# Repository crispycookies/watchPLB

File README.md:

# watchPLB
Open Source Emergency Beacon licensed under GPL-V3

Structure:
* Branch Samuel - Eagle Files
* Branch Firmware - Firmware files
  * In Firmware Directory there is a description of the folder Structure of the Firmware

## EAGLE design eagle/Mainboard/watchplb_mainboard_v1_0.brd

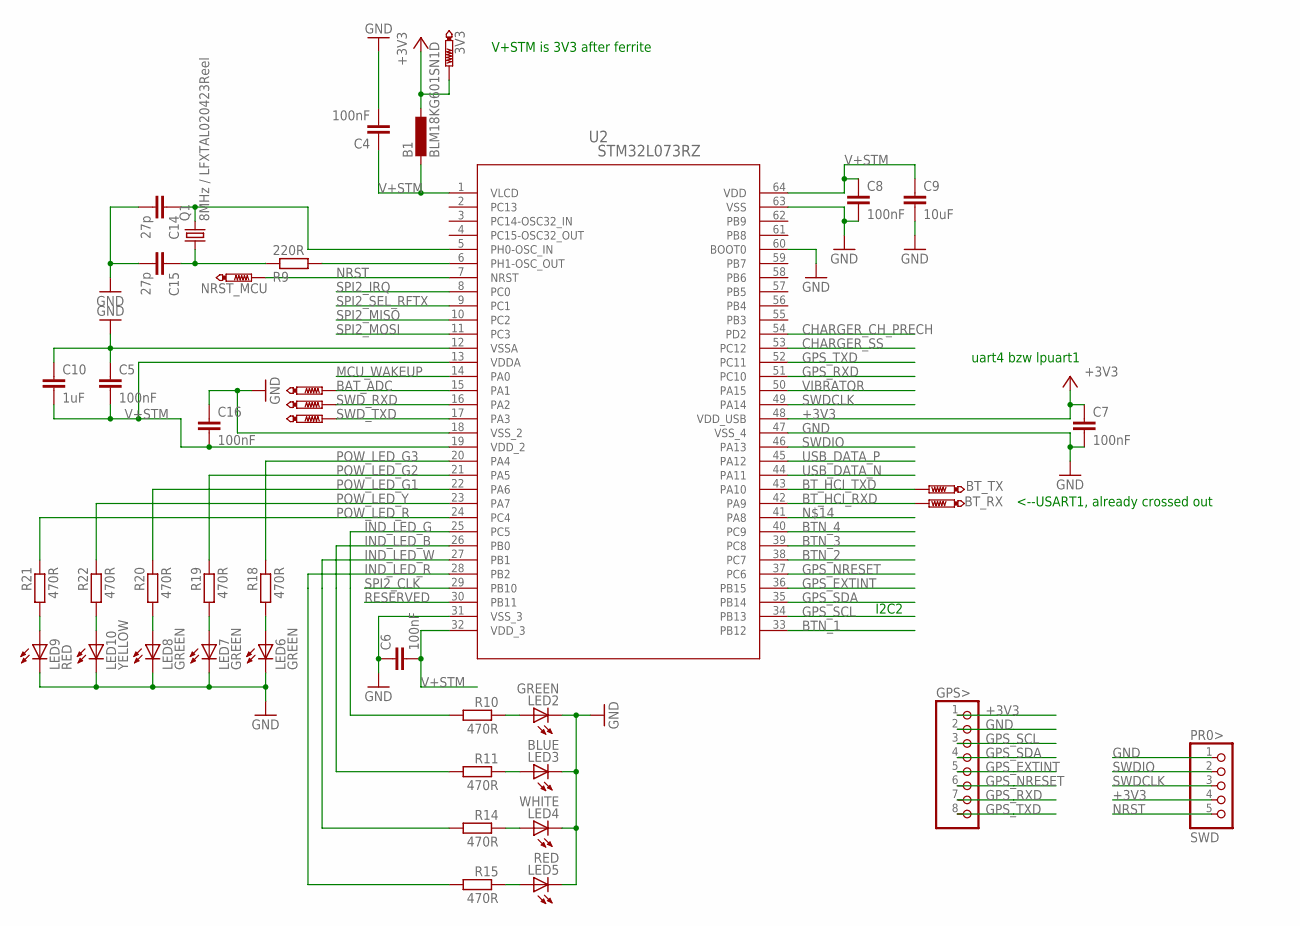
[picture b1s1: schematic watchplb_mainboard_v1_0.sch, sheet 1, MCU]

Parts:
3V3: PTR1B1,27; B1,27
B1: BLM18KG601SN1D; L0603
BAT_ADC: PTR1B1,27; B1,27
BT_RX: PTR1B1,27; B1,27
BT_TX: PTR1B1,27; B1,27
C4, C5, C6, C7, C8, C16: 100nF; C0805
C9: 10uF; C1206
C10: 1uF; C0805
C14, C15: 27p; C0805
GPS>: PINHD-1X8; 1X08
LED2, LED6, LED7, LED8: GREEN; CHIP-LED0805
LED3: BLUE; CHIP-LED0805
LED4: WHITE; CHIP-LED0805
LED5, LED9: RED; CHIP-LED0805
LED10: YELLOW; CHIP-LED0805
NRST_MCU: PTR1B1,27; B1,27
PR0>: SWD; 1X05
Q1: 8MHz / LFXTAL020423Reel; HC49UP
R9: 220R; M0805
R10, R11, R14, R15, R18, R19, R20, R21, R22: 470R; M0805
SWD_RXD: PTR1B1,27; B1,27
SWD_TXD: PTR1B1,27; B1,27
U2: STM32L073RZ; LQFP64-10X10MM

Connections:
+3V3: 3V3.TP, B1.1, C7.1, GPS>.1, PR0>.4, U2.48 (VDD_USB); also elsewhere on the board
BAT_ADC: BAT_ADC.TP, U2.15 (PA1); also elsewhere on the board
BTN_1: U2.33 (PB12); also elsewhere on the board
BTN_2: U2.38 (PC7); also elsewhere on the board
BTN_3: U2.39 (PC8); also elsewhere on the board
BTN_4: U2.40 (PC9); also elsewhere on the board
BT_HCI_RXD: BT_RX.TP, U2.42 (PA9); also elsewhere on the board
BT_HCI_TXD: BT_TX.TP, U2.43 (PA10); also elsewhere on the board
CHARGER_CH_PRECH: U2.54 (PD2); also elsewhere on the board
CHARGER_SS: U2.53 (PC12); also elsewhere on the board
GND: C4.2, C5.1, C6.1, C7.2, C8.2, C9.2, C10.1, C14.2, C15.2, C16.1, GPS>.2, LED2.C, LED3.C, LED4.C, LED5.C, LED6.C, LED7.C, LED8.C, LED9.C, LED10.C, PR0>.1, U2.12 (VSSA), U2.18 (VSS_2), U2.31 (VSS_3), U2.47 (VSS_4), U2.60 (BOOT0), U2.63 (VSS); also elsewhere on the board
GPS_EXTINT: GPS>.5, U2.36 (PB15)
GPS_NRESET: GPS>.6, U2.37 (PC6)
GPS_RXD: GPS>.7, U2.51 (PC10)
GPS_SCL: GPS>.3, U2.34 (PB13)
GPS_SDA: GPS>.4, U2.35 (PB14)
GPS_TXD: GPS>.8, U2.52 (PC11)
IND_LED_B: R11.2, U2.26 (PB0)
IND_LED_G: R10.2, U2.25 (PC5)
IND_LED_R: R15.2, U2.28 (PB2)
IND_LED_W: R14.2, U2.27 (PB1)
MCU_WAKEUP: U2.14 (PA0); also elsewhere on the board
unnamed: LED2.A, R10.1
unnamed: LED3.A, R11.1
unnamed: C15.1, Q1.1, R9.1
unnamed: C14.1, Q1.2, U2.5 (PH0-OSC_IN)
unnamed: R9.2, U2.6 (PH1-OSC_OUT)
unnamed: LED4.A, R14.1
unnamed: LED9.A, R21.2
unnamed: LED5.A, R15.1
unnamed: LED6.A, R18.2
unnamed: LED7.A, R19.2
unnamed: LED10.A, R22.2
unnamed: LED8.A, R20.2
NRST: NRST_MCU.TP, PR0>.5, U2.7 (NRST); also elsewhere on the board
POW_LED_G1: R20.1, U2.22 (PA6)
POW_LED_G2: R19.1, U2.21 (PA5)
POW_LED_G3: R18.1, U2.20 (PA4)
POW_LED_R: R21.1, U2.24 (PC4)
POW_LED_Y: R22.1, U2.23 (PA7)
RESERVED: U2.30 (PB11)
SPI2_CLK: U2.29 (PB10); also elsewhere on the board
SPI2_IRQ: U2.8 (PC0); also elsewhere on the board
SPI2_MISO: U2.10 (PC2); also elsewhere on the board
SPI2_MOSI: U2.11 (PC3); also elsewhere on the board
SPI2_SEL_RFTX: U2.9 (PC1); also elsewhere on the board
SWDCLK: PR0>.3, U2.49 (PA14)
SWDIO: PR0>.2, U2.46 (PA13)
SWD_RXD: SWD_RXD.TP, U2.16 (PA2)
SWD_TXD: SWD_TXD.TP, U2.17 (PA3)
USB_DATA_N: U2.44 (PA11); also elsewhere on the board
USB_DATA_P: U2.45 (PA12); also elsewhere on the board
V+STM: B1.2, C4.1, C5.2, C6.2, C8.1, C9.1, C10.2, C16.2, U2.1 (VLCD), U2.13 (VDDA), U2.19 (VDD_2), U2.32 (VDD_3), U2.64 (VDD)
VIBRATOR: U2.50 (PA15); also elsewhere on the board

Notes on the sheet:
<--USART1, already crossed out
I2C2
uart4 bzw lpuart1
V+STM is 3V3 after ferrite

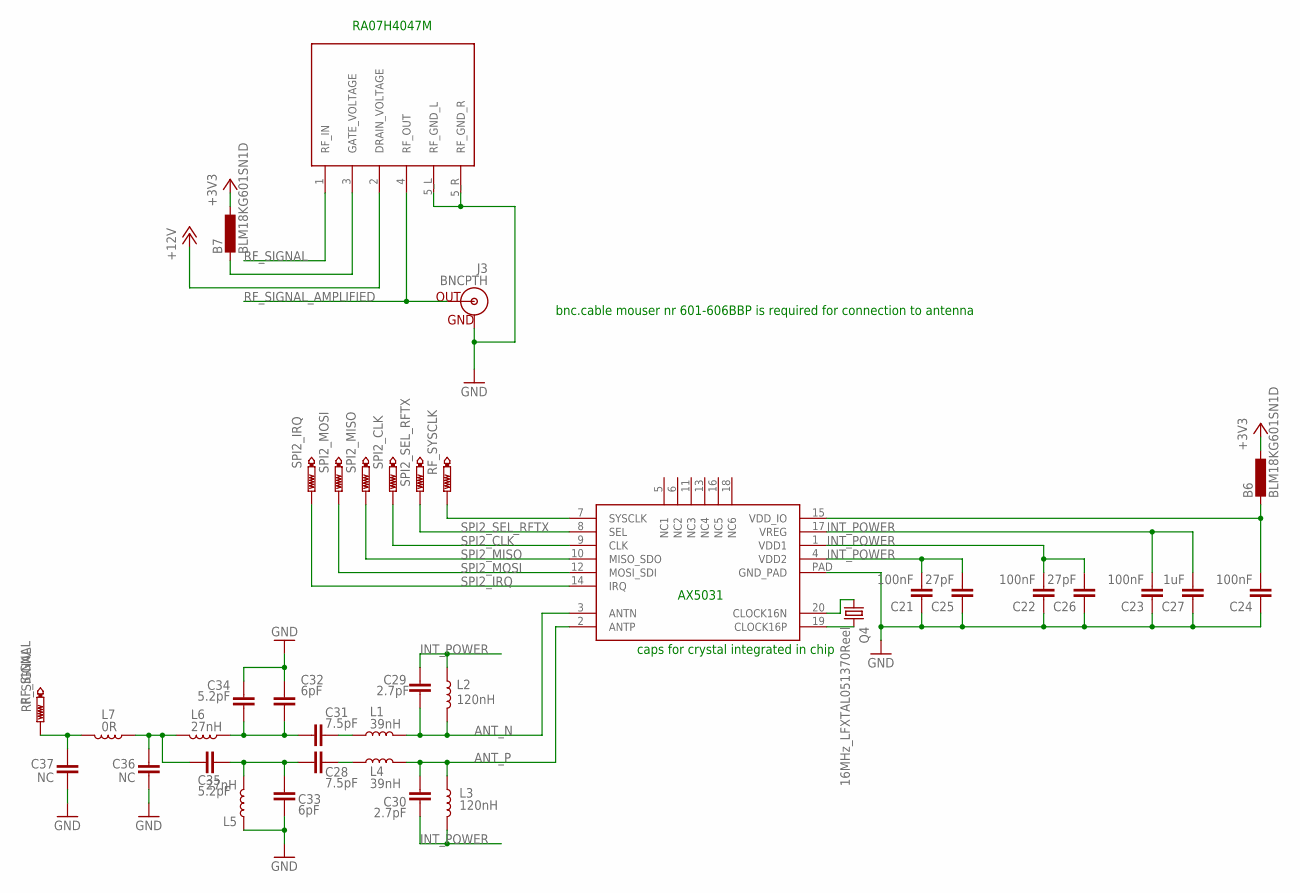
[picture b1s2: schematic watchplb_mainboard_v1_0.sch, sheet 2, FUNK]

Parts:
B6, B7: BLM18KG601SN1D; L0603
C21, C22, C23, C24: 100nF; C0805
C25, C26: 27pF; C0805
C27: 1uF; C0805
C28, C31: 7.5pF; C0805
C29, C30: 2.7pF; C0805
C32, C33: 6pF; C0805
C34, C35: 5.2pF; C0805
C36, C37: NC; C0805
IC4: AX5031; QFN20
J3: BNCPTH; BNC
L1, L4: 39nH; 0805
L2, L3: 120nH; 0805
L5, L6: 27nH; 0805
L7: 0R; 0805
Q4: 16MHz_LFXTAL051370Reel; HC49UP
RF_SIGNAL: PTR1B2,54; B2,54
RF_SYSCLK: PTR1B1,27; B1,27
SPI2_CLK, SPI2_IRQ, SPI2_MISO, SPI2_MOSI, SPI2_SEL_RFTX: PTR1B1,27; B1,27
U$2: RA07H4047M

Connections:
+3V3: B6.1, B7.1; also elsewhere on the board
+12V: U$2.2 (DRAIN_VOLTAGE); also elsewhere on the board
ANT_N: C29.1, IC4.3 (ANTN), L1.2, L2.2
ANT_P: C30.2, IC4.2 (ANTP), L3.1, L4.2
GND: C21.1, C22.1, C23.1, C24.1, C25.1, C26.1, C27.1, C32.1, C33.2, C34.1, C36.1, C37.1, IC4.PAD (GND_PAD), J3.GND, L5.1, U$2.5_L (RF_GND_L), U$2.5_R (RF_GND_R); also elsewhere on the board
INT_POWER: C21.2, C22.2, C23.2, C25.2, C26.2, C27.2, C29.2, C30.1, IC4.1 (VDD1), IC4.4 (VDD2), IC4.17 (VREG), L2.1, L3.2
unnamed: IC4.19 (CLOCK16P), Q4.2
unnamed: IC4.20 (CLOCK16N), Q4.1
unnamed: IC4.7 (SYSCLK), RF_SYSCLK.TP
unnamed: C28.1, L4.1
unnamed: C31.1, L1.1
unnamed: C31.2, C32.2, C34.2, L6.1
unnamed: C28.2, C33.1, C35.2, L5.2
unnamed: C35.1, C36.2, L6.2, L7.1
unnamed: B6.2, C24.2, IC4.15 (VDD_IO)
unnamed: B7.2, U$2.3 (GATE_VOLTAGE)
RF_SIGNAL: C37.2, L7.2, RF_SIGNAL.TP, U$2.1 (RF_IN)
RF_SIGNAL_AMPLIFIED: J3.S (OUT), U$2.4 (RF_OUT)
SPI2_CLK: IC4.9 (CLK), SPI2_CLK.TP; also elsewhere on the board
SPI2_IRQ: IC4.14 (IRQ), SPI2_IRQ.TP; also elsewhere on the board
SPI2_MISO: IC4.10 (MISO_SDO), SPI2_MISO.TP; also elsewhere on the board
SPI2_MOSI: IC4.12 (MOSI_SDI), SPI2_MOSI.TP; also elsewhere on the board
SPI2_SEL_RFTX: IC4.8 (SEL), SPI2_SEL_RFTX.TP; also elsewhere on the board

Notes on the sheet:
caps for crystal integrated in chip
bnc.cable mouser nr 601-606BBP is required for connection to antenna
AX5031
RA07H4047M

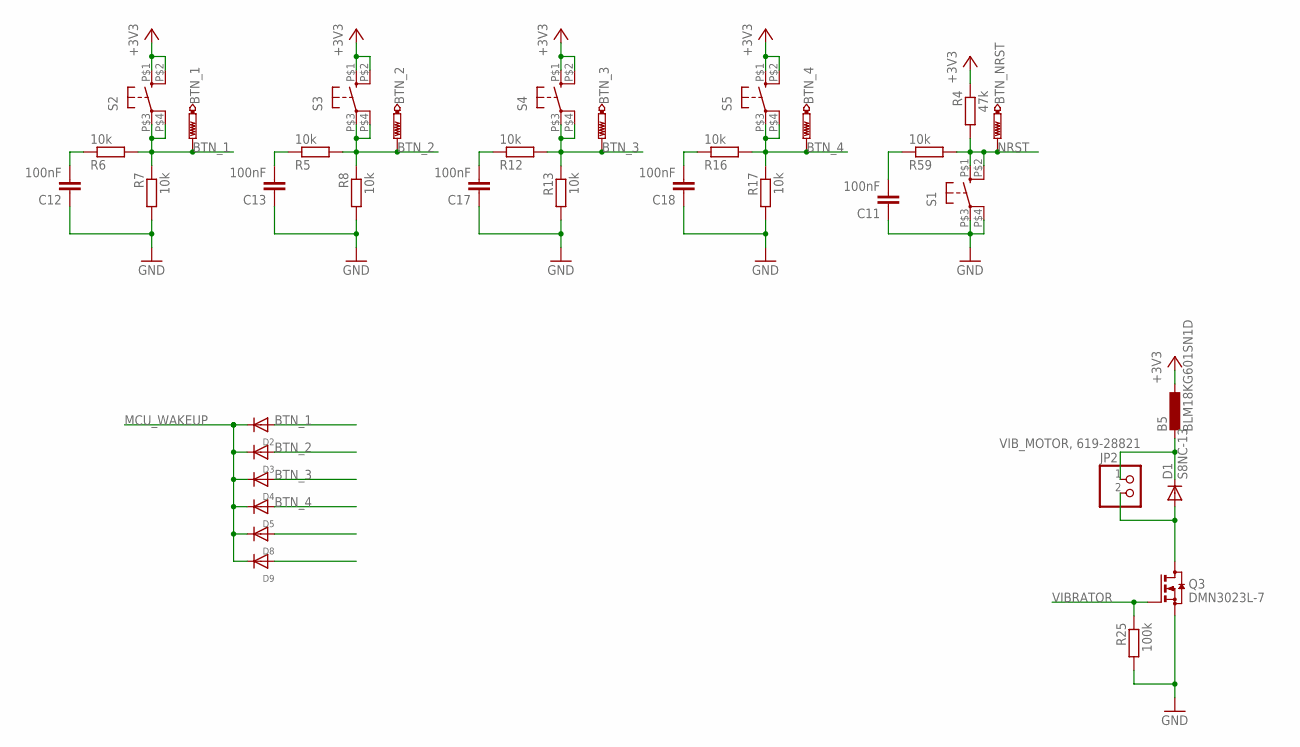
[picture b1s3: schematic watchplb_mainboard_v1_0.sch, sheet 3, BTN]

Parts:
B5: BLM18KG601SN1D; L0603
BTN_1, BTN_2, BTN_3, BTN_4: PTR1B1,27; B1,27
BTN_NRST: PTR1B1,27; B1,27
C11, C12, C13, C17, C18: 100nF; C0805
D1: S8NC-13; SMC
D2, D3, D4, D5, D8, D9: DIODESOD-123; SOD-123
JP2: VIB_MOTOR, 619-28821; 1X02
Q3: DMN3023L-7; SOT23
R4: 47k; M0805
R5, R6, R7, R8, R12, R13, R16, R17, R59: 10k; M0805
R25: 100k; M0805
S1, S2, S3, S4, S5: TL3305; SMD_SWITCH

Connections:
+3V3: B5.1, R4.1, S2.P$1 (SL1), S2.P$2 (SL2), S3.P$1 (SL1), S3.P$2 (SL2), S4.P$1 (SL1), S4.P$2 (SL2), S5.P$1 (SL1), S5.P$2 (SL2); also elsewhere on the board
BTN_1: BTN_1.TP, D2.A, R6.2, R7.1, S2.P$3 (SR1), S2.P$4 (SR2); also elsewhere on the board
BTN_2: BTN_2.TP, D3.A, R5.2, R8.1, S3.P$3 (SR1), S3.P$4 (SR2); also elsewhere on the board
BTN_3: BTN_3.TP, D4.A, R12.2, R13.1, S4.P$3 (SR1), S4.P$4 (SR2); also elsewhere on the board
BTN_4: BTN_4.TP, D5.A, R16.2, R17.1, S5.P$3 (SR1), S5.P$4 (SR2); also elsewhere on the board
GND: C11.1, C12.1, C13.1, C17.1, C18.1, Q3.2 (S), R7.2, R8.2, R13.2, R17.2, R25.2, S1.P$3 (SR1), S1.P$4 (SR2); also elsewhere on the board
MCU_WAKEUP: D2.C, D3.C, D4.C, D5.C, D8.C, D9.C; also elsewhere on the board
unnamed: C12.2, R6.1
unnamed: C13.2, R5.1
unnamed: C17.2, R12.1
unnamed: C18.2, R16.1
unnamed: D1.A, JP2.2, Q3.3 (D)
unnamed: B5.2, D1.C, JP2.1
unnamed: C11.2, R59.1
NRST: BTN_NRST.TP, R4.2, R59.2, S1.P$1 (SL1), S1.P$2 (SL2); also elsewhere on the board
VIBRATOR: Q3.1 (G), R25.1; also elsewhere on the board

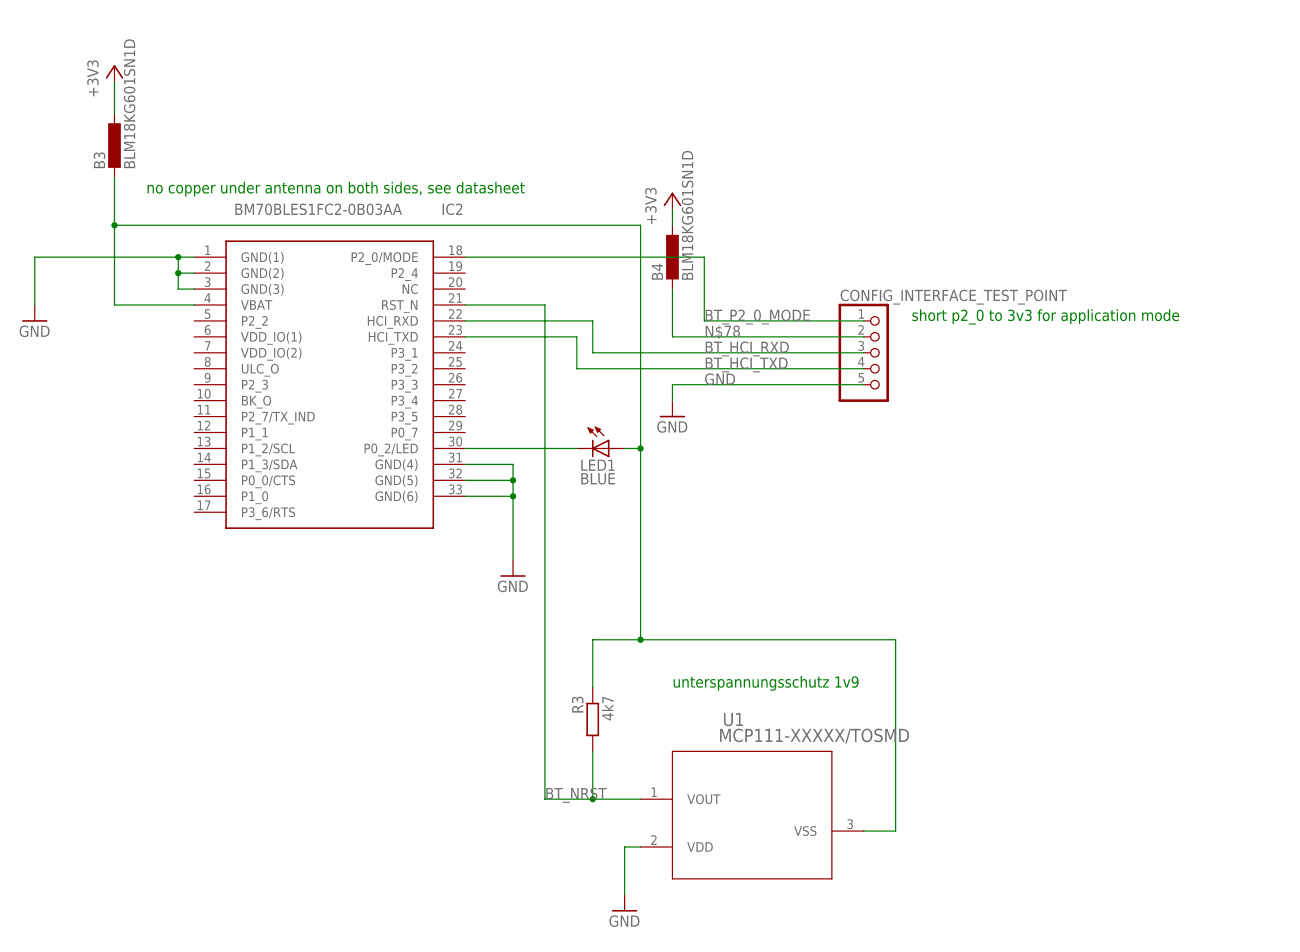
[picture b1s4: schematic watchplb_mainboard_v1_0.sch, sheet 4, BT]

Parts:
B3, B4: BLM18KG601SN1D; L0603
CONFIG_INTERFACE_TEST_POINT: PINHD-1X5; 1X05
IC2: BM70BLES1FC2-0B03AA; BM78SPPS5NC2_1
LED1: BLUE; CHIP-LED0805
R3: 4k7; M0805
U1: MCP111-XXXXX/TOSMD; SC70-3-R

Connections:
+3V3: B3.1, B4.1; also elsewhere on the board
BT_HCI_RXD: CONFIG_INTERFACE_TEST_POINT.3, IC2.22 (HCI_RXD); also elsewhere on the board
BT_HCI_TXD: CONFIG_INTERFACE_TEST_POINT.4, IC2.23 (HCI_TXD); also elsewhere on the board
BT_NRST: IC2.21 (RST_N), R3.2, U1.1 (VOUT)
BT_P2_0_MODE: CONFIG_INTERFACE_TEST_POINT.1, IC2.18 (P2_0/MODE)
GND: CONFIG_INTERFACE_TEST_POINT.5, IC2.1 (GND(1)), IC2.2 (GND(2)), IC2.3 (GND(3)), IC2.31 (GND(4)), IC2.32 (GND(5)), IC2.33 (GND(6)), U1.2 (VDD); also elsewhere on the board
unnamed: IC2.30 (P0_2/LED), LED1.C
unnamed: B4.2, CONFIG_INTERFACE_TEST_POINT.2
unnamed: B3.2, IC2.4 (VBAT), LED1.A, R3.1, U1.3 (VSS)

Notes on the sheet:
unterspannungsschutz 1v9
no copper under antenna on both sides, see datasheet
short p2_0 to 3v3 for application mode

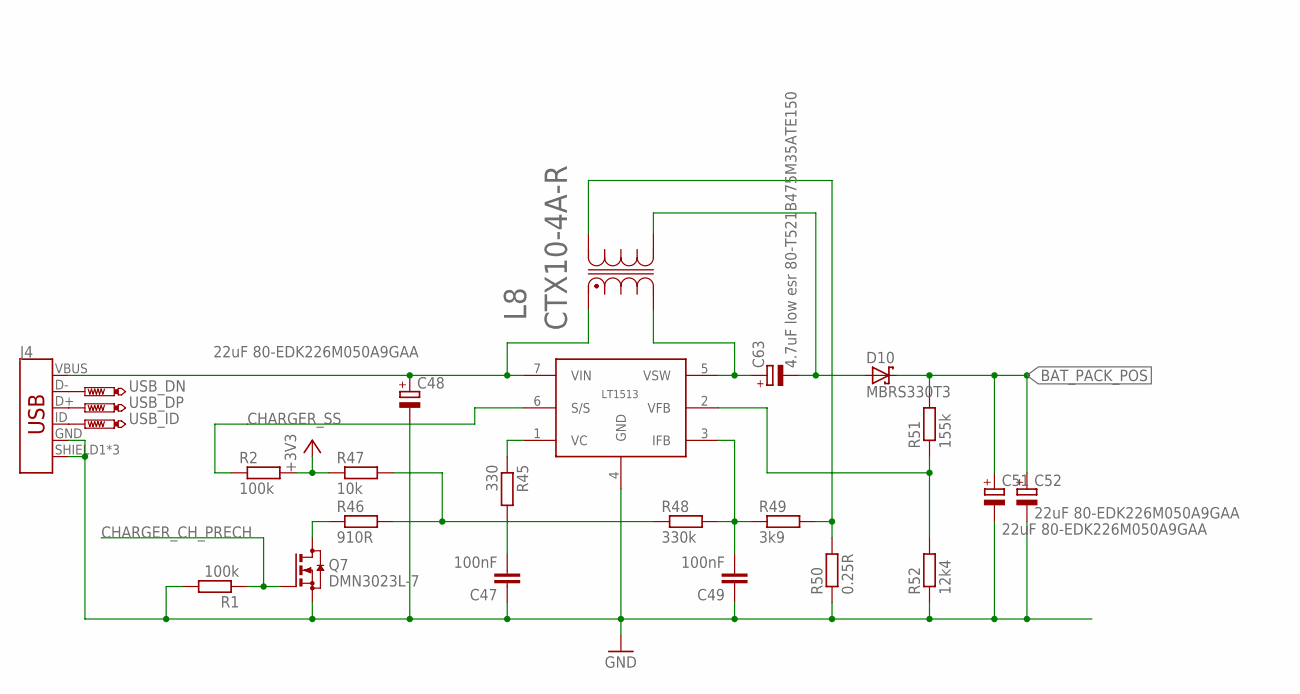
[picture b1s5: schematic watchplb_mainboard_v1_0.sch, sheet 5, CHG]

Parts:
C47, C49: 100nF; C0805K
C48, C51, C52: 22uF 80-EDK226M050A9GAA; PANASONIC_E
C63: 4.7uF low esr 80-T521B475M35ATE150; B/3528-21R
D10: MBRS330T3; SMC
IC1: LT1513; TO220-7
J4: USB_MICRO-B_FEMALE-SMT; USB-B-MICRO-SMD
L8: CTX10-4A-R; INDM115115X635N
Q7: DMN3023L-7; SOT23
R1, R2: 100k; M0805
R45: 330; M0805
R46: 910R; M0805
R47: 10k; M0805
R48: 330k; M0805
R49: 3k9; M0805
R50: 0.25R; R2512
R51: 155k; M0805
R52: 12k4; M0805
USB_DN: PTR1B1,27; B1,27
USB_DP: PTR1B1,27; B1,27
USB_ID: PTR1B1,27; B1,27

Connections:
+3V3: R2.2, R47.1; also elsewhere on the board
BAT_PACK_POS: C51.+, C52.+, D10.C, R51.2; also elsewhere on the board
CHARGER_CH_PRECH: Q7.1 (G), R1.1; also elsewhere on the board
CHARGER_SS: IC1.6 (S/S), R2.1; also elsewhere on the board
GND: C47.1, C48.-, C49.1, C51.-, C52.-, IC1.4 (GND), J4.GND, J4.SHIELD1 (SHIELD), J4.SHIELD2 (SHIELD), J4.SHIELD3 (SHIELD), Q7.2 (S), R1.2, R50.1, R52.1; also elsewhere on the board
unnamed: C63.+, IC1.5 (VSW), L8.2
unnamed: C48.+, IC1.7 (VIN), J4.VBUS, L8.1
unnamed: L8.4, R49.2, R50.2
unnamed: C47.2, R45.2
unnamed: IC1.1 (VC), R45.1
unnamed: Q7.3 (D), R46.1
unnamed: R46.2, R47.2, R48.1
unnamed: C49.2, IC1.3 (IFB), R48.2, R49.1
unnamed: IC1.2 (VFB), R51.1, R52.2
unnamed: J4.ID, USB_ID.TP
unnamed: J4.D+, USB_DP.TP
unnamed: J4.D-, USB_DN.TP
unnamed: C63.-, D10.A, L8.3

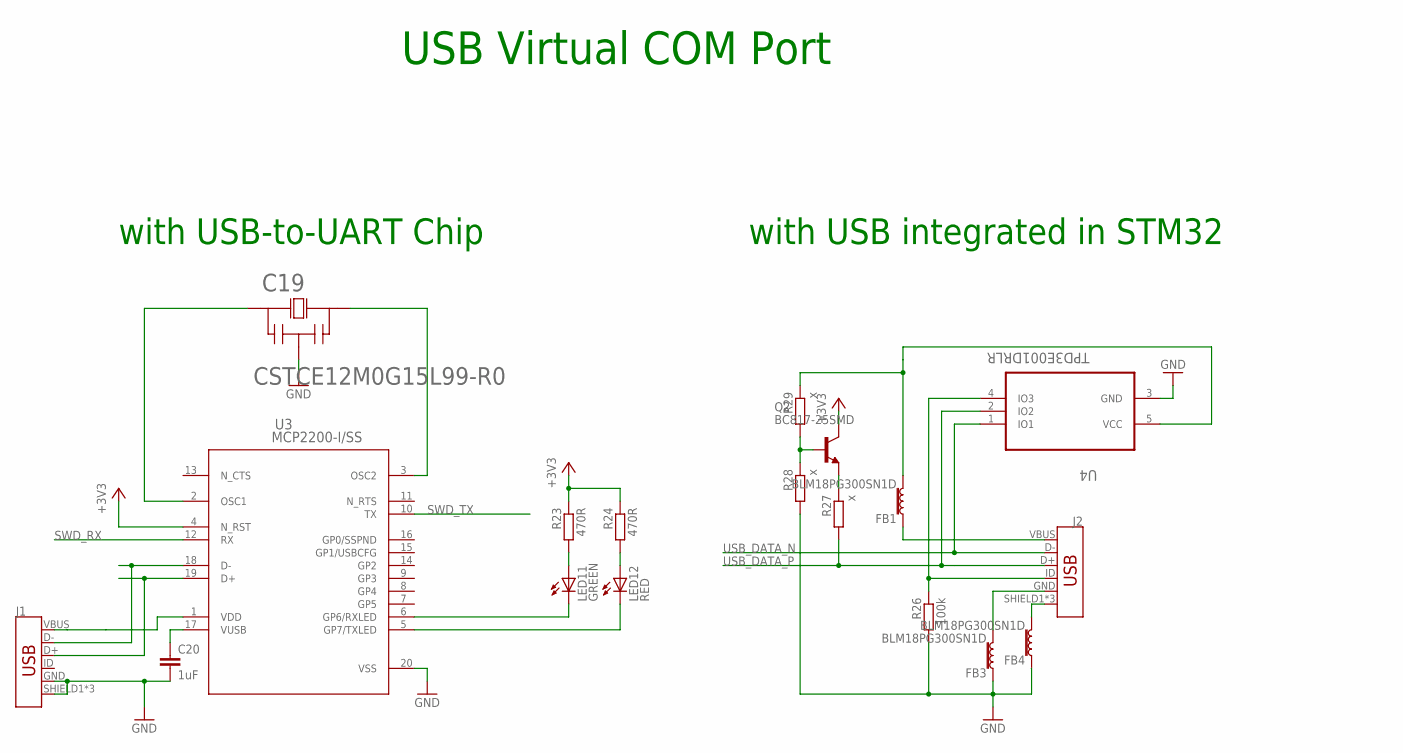
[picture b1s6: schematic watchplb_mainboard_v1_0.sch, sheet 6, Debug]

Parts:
C19: CSTCE12M0G15L99-R0; CSTCE
C20: 1uF; C0805
FB1, FB3, FB4: BLM18PG300SN1D; 0603
J1, J2: USB_MICRO-B_FEMALE-SMT; USB-B-MICRO-SMD
LED11: GREEN; CHIP-LED0805
LED12: RED; CHIP-LED0805
Q2: BC817-25SMD; SOT23-BEC
R23, R24: 470R; M0805
R26: 100k; M0805
R27, R28, R29: x; M0805
U3: MCP2200-I/SS; SSOP20_MC
U4: TPD3E001DRLR; SOT50P160X60-5N

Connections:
+3V3: Q2.C, R23.1, R24.1, U3.4 (N_RST); also elsewhere on the board
GND: C19.2 (22), C20.2, FB3.1, FB4.1, J1.GND, J1.SHIELD1 (SHIELD), J1.SHIELD2 (SHIELD), J1.SHIELD3 (SHIELD), R26.2, R28.2, U3.20 (VSS), U4.3 (GND); also elsewhere on the board
unnamed: LED11.A, R23.2
unnamed: C19.3 (33), U3.3 (OSC2)
unnamed: C19.1 (11), U3.2 (OSC1)
unnamed: J1.D-, U3.18 (D-)
unnamed: J1.D+, U3.19 (D+)
unnamed: C20.1, U3.17 (VUSB)
unnamed: LED12.A, R24.2
unnamed: LED11.C, U3.6 (GP6/RXLED)
unnamed: LED12.C, U3.5 (GP7/TXLED)
unnamed: FB4.2, J2.SHIELD1 (SHIELD), J2.SHIELD2 (SHIELD), J2.SHIELD3 (SHIELD)
unnamed: FB3.2, J2.GND
unnamed: FB1.1, J2.VBUS
unnamed: J2.ID, R26.1, U4.4 (IO3)
unnamed: Q2.E, R27.1
unnamed: Q2.B, R28.1, R29.2
unnamed: J1.VBUS, U3.1 (VDD)
unnamed: FB1.2, R29.1, U4.5 (VCC)
SWD_RX: U3.12 (RX)
SWD_TX: U3.10 (TX)
USB_DATA_N: J2.D-, U4.1 (IO1); also elsewhere on the board
USB_DATA_P: J2.D+, R27.2, U4.2 (IO2); also elsewhere on the board

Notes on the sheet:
USB Virtual COM Port
with USB integrated in STM32
with USB-to-UART Chip

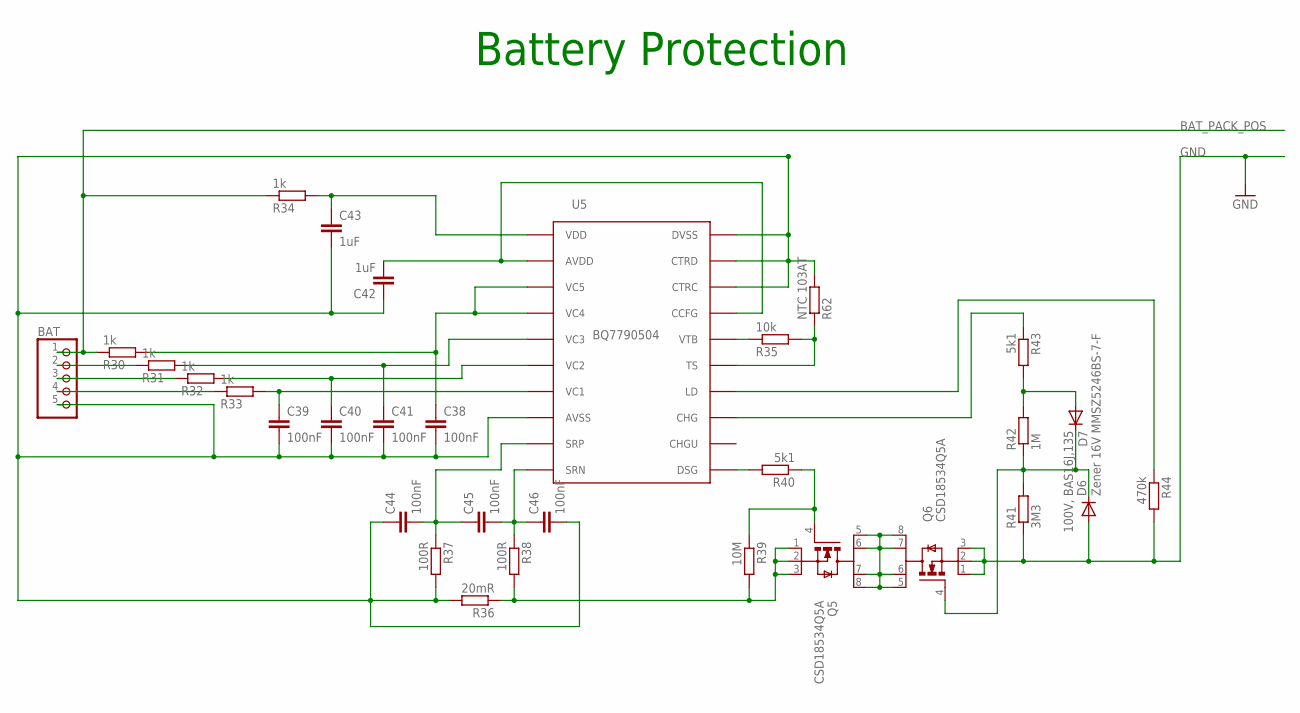
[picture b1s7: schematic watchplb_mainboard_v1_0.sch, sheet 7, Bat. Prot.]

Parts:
BAT: PINHD-1X5; 1X05
C38, C39, C40, C41, C44, C45, C46: 100nF; C0805K
C42, C43: 1uF; C0805K
D6: Zener 16V MMSZ5246BS-7-F; SOD323-R
D7: 100V, BAS16J,135; SOD323-R
Q5, Q6: CSD18534Q5A; TRANS_CSD18534Q5A
R30, R31, R32, R33, R34: 1k; M0805
R35: 10k; M0805
R36: 20mR; R2512
R37, R38: 100R; M0805
R39: 10M; M0805
R40, R43: 5k1; M0805
R41: 3M3; M0805
R42: 1M; M0805
R44: 470k; M0805
R62: NTC 103AT; M0805
U5: BQ7790504; TSSOP-20/6MM

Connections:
BAT_PACK_GND: BAT.5, C38.2, C39.2, C40.2, C41.2, C42.1, C43.2, C44.1, C46.2, R36.2, R37.2, R62.2, U5.8 (AVSS), U5.18 (CTRC), U5.19 (CTRD), U5.20 (DVSS)
BAT_PACK_POS: BAT.1, R30.1, R34.1; also elsewhere on the board
GND: D6.A, Q6.1, Q6.2, Q6.3, R41.1, R44.2; also elsewhere on the board
unnamed: R35.2, R62.1, U5.15 (TS)
unnamed: D6.C, D7.C, Q6.4, R41.2, R42.1
unnamed: BAT.2, R31.1
unnamed: BAT.3, R32.1
unnamed: BAT.4, R33.1
unnamed: C39.1, R33.2, U5.7 (VC1)
unnamed: C40.1, R32.2, U5.6 (VC2)
unnamed: C41.1, R31.2, U5.5 (VC3)
unnamed: C38.1, R30.2, U5.3 (VC5), U5.4 (VC4)
unnamed: C43.1, R34.2, U5.1 (VDD)
unnamed: Q5.1, Q5.2, Q5.3, R36.1, R38.2, R39.2
unnamed: C42.2, U5.2 (AVDD), U5.17 (CCFG)
unnamed: C45.2, C46.1, R38.1, U5.10 (SRN)
unnamed: C44.2, C45.1, R37.1, U5.9 (SRP)
unnamed: Q5.5, Q5.6, Q5.7, Q5.8, Q6.5, Q6.6, Q6.7, Q6.8
unnamed: R35.1, U5.16 (VTB)
unnamed: Q5.4, R39.1, R40.1
unnamed: R40.2, U5.11 (DSG)
unnamed: D7.A, R42.2, R43.2
unnamed: R43.1, U5.13 (CHG)
unnamed: R44.1, U5.14 (LD)

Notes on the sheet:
BQ7790504
Battery Protection

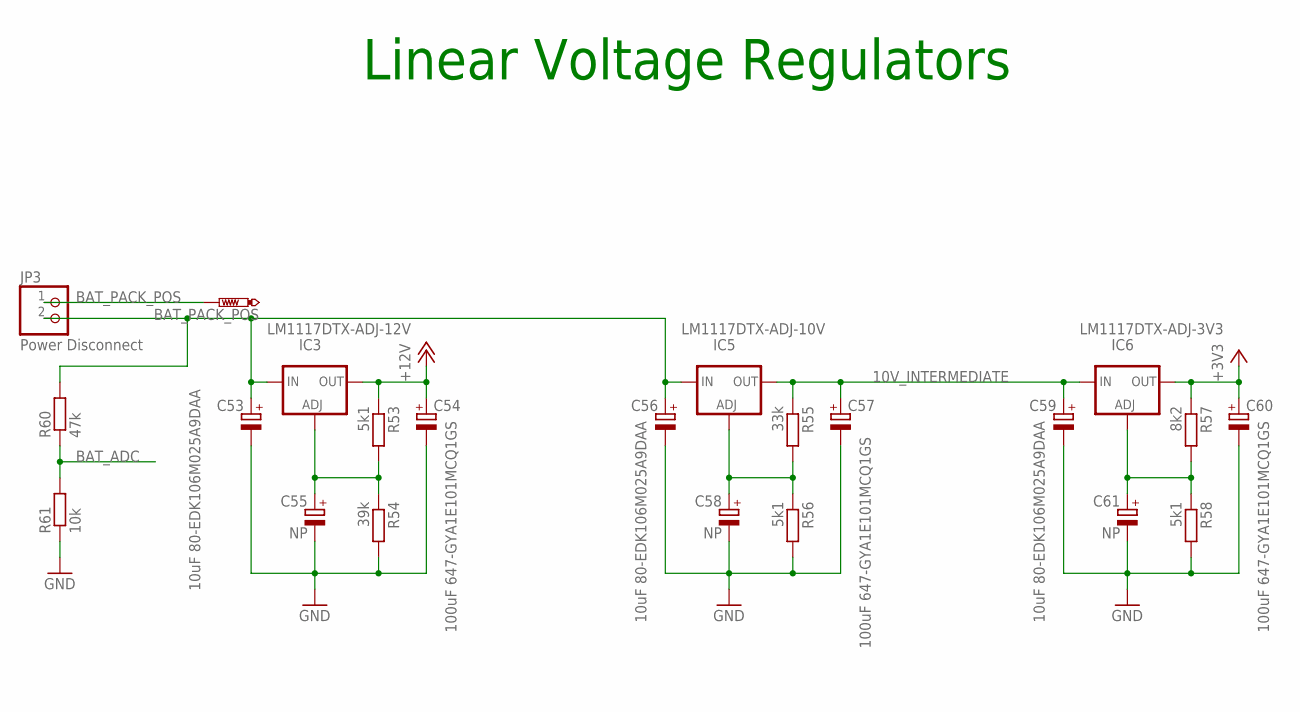
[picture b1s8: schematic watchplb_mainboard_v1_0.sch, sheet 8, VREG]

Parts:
BAT_PACK_POS: PTR1B1,27; B1,27
C53, C56, C59: 10uF 80-EDK106M025A9DAA; PANASONIC_E
C54, C57, C60: 100uF 647-GYA1E101MCQ1GS; PANASONIC_E
C55, C58, C61: NP; PANASONIC_E
IC3: LM1117DTX-ADJ-12V; TO252
IC5: LM1117DTX-ADJ-10V; TO252
IC6: LM1117DTX-ADJ-3V3; TO252
JP3: Power Disconnect; 1X02
R53, R56, R58: 5k1; M0805
R54: 39k; M0805
R55: 33k; M0805
R57: 8k2; M0805
R60: 47k; M0805
R61: 10k; M0805

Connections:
10V_INTERMEDIATE: C57.+, C59.+, IC5.TAB (OUT), IC6.2 (IN), R55.1
+3V3: C60.+, IC6.TAB (OUT), R57.1; also elsewhere on the board
+12V: C54.+, IC3.TAB (OUT), R53.1; also elsewhere on the board
BAT_ADC: R60.1, R61.2; also elsewhere on the board
BAT_PACK_POS: BAT_PACK_POS.TP, JP3.1; also elsewhere on the board
GND: C53.-, C54.-, C55.-, C56.-, C57.-, C58.-, C59.-, C60.-, C61.-, R54.2, R56.2, R58.2, R61.1; also elsewhere on the board
unnamed: C53.+, C56.+, IC3.2 (IN), IC5.2 (IN), JP3.2, R60.2
unnamed: C55.+, IC3.1 (ADJ), R53.2, R54.1
unnamed: C58.+, IC5.1 (ADJ), R55.2, R56.1
unnamed: C61.+, IC6.1 (ADJ), R57.2, R58.1

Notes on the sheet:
Linear Voltage Regulators

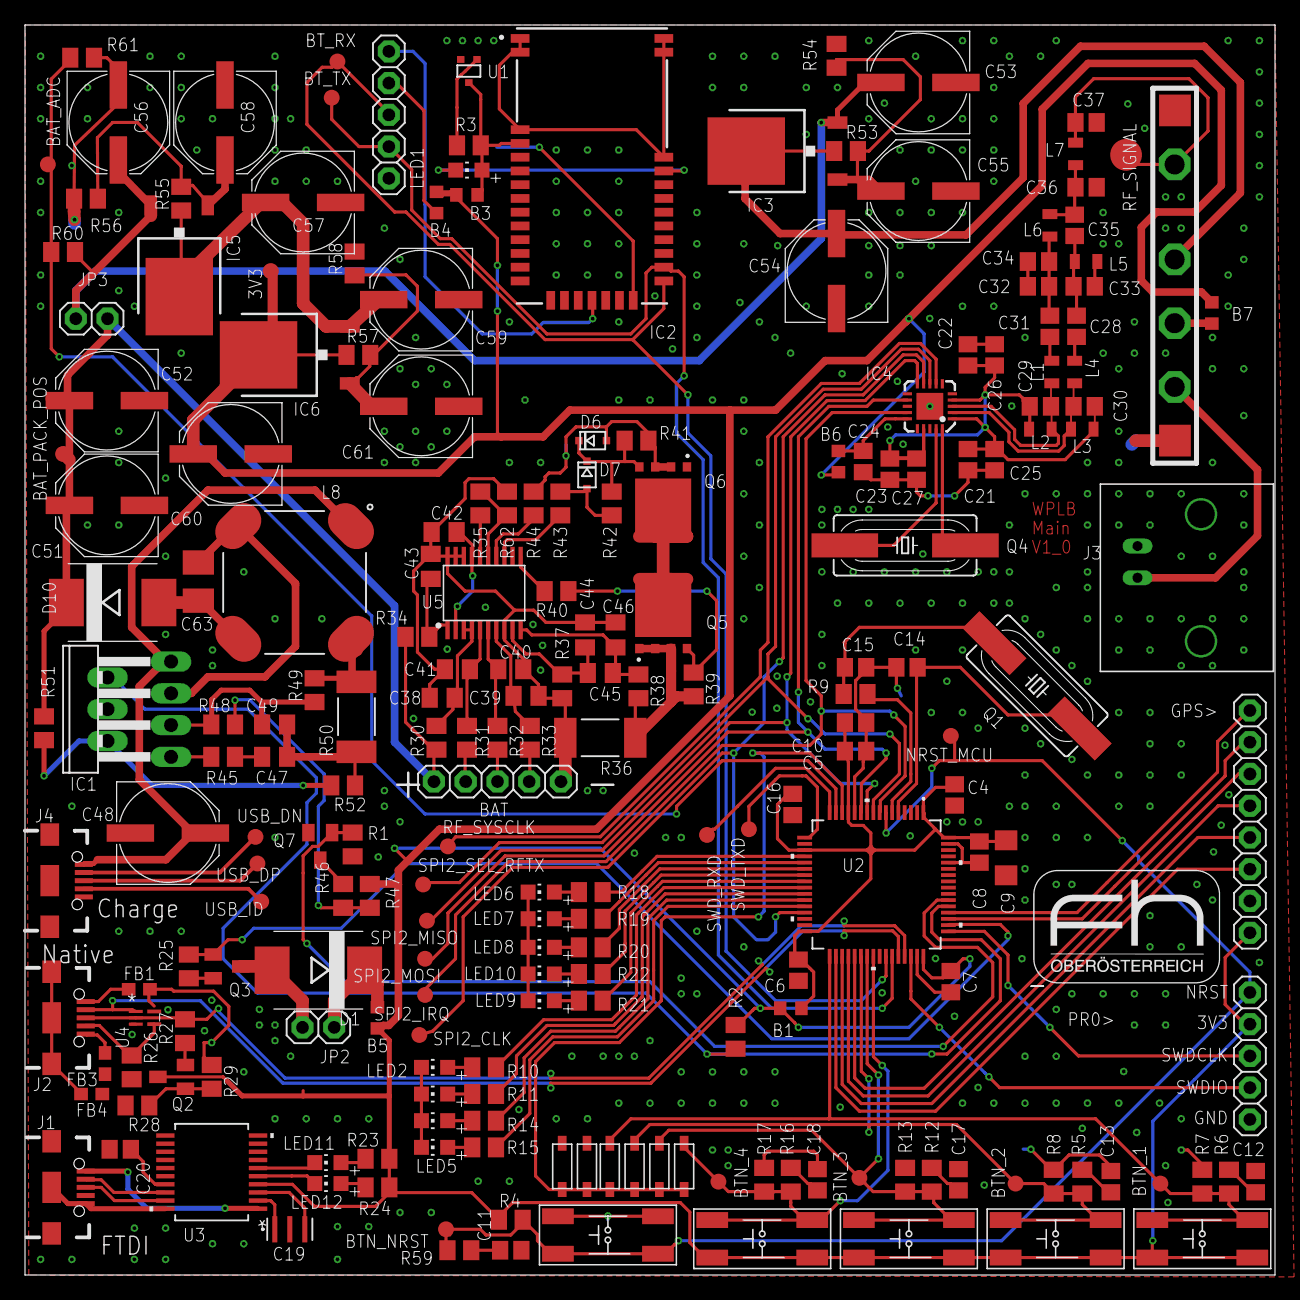
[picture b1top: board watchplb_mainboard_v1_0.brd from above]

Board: 2 copper layers, 100.0 x 100.0 mm, 218 parts (1 on the bottom side), 139 nets.

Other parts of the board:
U$4: FH_LOGO
U$5: FH_LOGO_050

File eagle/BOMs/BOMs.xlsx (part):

Qty | Value | Device | Package | Parts | Description | AVAILABILITY | DESCRIPTION.1 | DIGIKEY | HEIGHT | MANUFACTURER_NAME | MANUFACTURER_PART_NUMBER | MF | MOUSER-NR | MP | MPN | OC_FARNELL | OC_NEWARK | PACKAGE.1 | PRICE | PROD_ID | RS_PART_NUMBER | SF_ID | SUPPLIER | TP_SIGNAL_NAME | VALUE.1 | VENDOR | Column1
6 |  | DIODESOD-123 | SOD-123 | D2, D3, D4, D5, D8, D9 | Diode
2 |  | PINHD-1X5 | 1X05 | BAT, CONFIG_INTERFACE_TEST_POINT | PIN HEADER
1 |  | PINHD-1X8 | 1X08 | GPS> | PIN HEADER
5 |  | TL3305 | SMD_SWITCH | S1, S2, S3, S4, S5 | OMRON SWITCH |  |  |  |  |  |  |  | 612-TL3305AF260QG |  | TL3305
3 |  | USB_MICRO-B_FEMALE-SMT | USB-B-MICRO-SMD | J1, J2, J4 | USB Type Micro-B Connector |  |  |  |  |  |  |  |  |  |  |  |  |  |  | CONN-11752
1 | 0.25R | R-EU_R2512 | R2512 | R50 | RESISTOR, European symbol
1 | 0R | INDUCTOR-0805-3.3UH | 0805 | L7 | Inductors |  |  |  |  |  |  |  |  |  |  |  |  |  |  | NDUC-13076 |  |  |  |  | 3.3µH/±20%/450mA
2 | 100R | R-EU_M0805 | M0805 | R37, R38 | RESISTOR, European symbol
1 | 100V, BAS16J,135 | DIODE-SOD323-R | SOD323-R | D7 | DIODE
2 | 100k | R-EU_M0805 | M0805 | R25, R26 | RESISTOR, European symbol
15 | 100nF | C-EUC0805 | C0805 | C4, C5, C6, C7, C8, C11, C12, C13, C16, C17, C18, C21, C22, C23, C24 | CAPACITOR, European symbol
9 | 100nF | C-EUC0805K | C0805K | C38, C39, C40, C41, C44, C45, C46, C47, C49 | CAPACITOR, European symbol
3 | 100uF 647-GYA1E101MCQ1GS | CPOL-EUE | PANASONIC_E | C54, C57, C60 | POLARIZED CAPACITOR, European symbol
1 | 10M | R-EU_M0805 | M0805 | R39 | RESISTOR, European symbol
13 | 10k | R-EU_M0805 | M0805 | R5, R6, R7, R8, R12, R13, R16, R17, R35, R47, R49, R59, R61 | RESISTOR, European symbol
1 | 10uF | C-EUC1206 | C1206 | C9 | CAPACITOR, European symbol
3 | 10uF 80-EDK106M025A9DAA | CPOL-EUE | PANASONIC_E | C53, C56, C59 | POLARIZED CAPACITOR, European symbol
1 | 120k | R-EU_M0805 | M0805 | R51 | RESISTOR, European symbol
2 | 120nH | INDUCTOR-0805-3.3UH | 0805 | L2, L3 | Inductors |  |  |  |  |  |  |  |  |  |  |  |  |  |  | NDUC-13076 |  |  |  |  | 3.3µH/±20%/450mA
1 | 12k4 | R-EU_M0805 | M0805 | R52 | RESISTOR, European symbol
1 | 16MHz_LFXTAL051370Reel | CRYSTALHC49UP | HC49UP | Q4 | CRYSTAL |  |  |  |  |  |  |  |  |  |  | unknown | unknown
1 | 1M | R-EU_M0805 | M0805 | R42 | RESISTOR, European symbol
5 | 1k | R-EU_M0805 | M0805 | R30, R31, R32, R33, R34 | RESISTOR, European symbol
3 | 1uF | C-EUC0805 | C0805 | C10, C20, C27 | CAPACITOR, European symbol
2 | 1uF | C-EUC0805K | C0805K | C42, C43 | CAPACITOR, European symbol
2 | 2.7pF | C-EUC0805 | C0805 | C29, C30 | CAPACITOR, European symbol
1 | 20mR | R-EU_R2512 | R2512 | R36 | RESISTOR, European symbol
3 | 220R | R-EU_M0805 | M0805 | R9, R23, R24 | RESISTOR, European symbol
3 | 22uF 80-EDK226M050A9GAA | CPOL-EUE | PANASONIC_E | C48, C51, C52 | POLARIZED CAPACITOR, European symbol
2 | 27nH | INDUCTOR-0805-3.3UH | 0805 | L5, L6 | Inductors |  |  |  |  |  |  |  |  |  |  |  |  |  |  | NDUC-13076 |  |  |  |  | 3.3µH/±20%/450mA
2 | 27p | C-EUC0805 | C0805 | C14, C15 | CAPACITOR, European symbol
2 | 27pF | C-EUC0805 | C0805 | C25, C26 | CAPACITOR, European symbol
1 | 330 | R-EU_M0805 | M0805 | R45 | RESISTOR, European symbol
1 | 330k | R-EU_M0805 | M0805 | R48 | RESISTOR, European symbol
2 | 39nH | INDUCTOR-0805-3.3UH | 0805 | L1, L4 | Inductors |  |  |  |  |  |  |  |  |  |  |  |  |  |  | NDUC-13076 |  |  |  |  | 3.3µH/±20%/450mA
1 | 3M3 | R-EU_M0805 | M0805 | R41 | RESISTOR, European symbol
1 | 4.7uF low esr 80-T521B475M35ATE150 | CPOL-EUB/3528-21R | B/3528-21R | C63 | POLARIZED CAPACITOR, European symbol
9 | 470R | R-EU_M0805 | M0805 | R10, R11, R14, R15, R18, R19, R20, R21, R22 | RESISTOR, European symbol
1 | 470k | R-EU_M0805 | M0805 | R44 | RESISTOR, European symbol
5 | 47k | R-EU_M0805 | M0805 | R4, R54, R56, R58, R60 | RESISTOR, European symbol
1 | 4k7 | R-EU_M0805 | M0805 | R3 | RESISTOR, European symbol
2 | 5.2pF | C-EUC0805 | C0805 | C34, C35 | CAPACITOR, European symbol
5 | 5k1 | R-EU_M0805 | M0805 | R40, R43, R53, R55, R57 | RESISTOR, European symbol
2 | 6pF | C-EUC0805 | C0805 | C32, C33 | CAPACITOR, European symbol
2 | 7.5pF | C-EUC0805 | C0805 | C28, C31 | CAPACITOR, European symbol
1 | 8MHz / LFXTAL020423Reel | CRYSTALHC49UP | HC49UP | Q1 | CRYSTAL |  |  |  |  |  |  |  |  |  |  | unknown | unknown
1 | 910R | R-EU_M0805 | M0805 | R46 | RESISTOR, European symbol
1 | AX5031 | AX5031 | QFN20 | IC4 | AX5031 RF Transmitter 400-470MHz 800-940MHz
1 | BC817-25SMD | BC817-25SMD | SOT23-BEC | Q2 | NPN Transistor
6 | BLM18KG601SN1D | B-EU_B0603 | L0603 | B1, B3, B4, B5, B6, B7 | EMI Filter
3 | BLM18PG300SN1D | FERRITE_BEAD-0603 | 0603 | FB1, FB3, FB4 | Ferrite Bead (blocks, cores, rings, chokes, etc.) |  |  |  |  |  |  |  |  |  |  |  |  |  |  | NDUC-13805 |  |  |  |  | 30O/1.8A
2 | BLUE | LEDCHIP-LED0805 | CHIP-LED0805 | LED1, LED3 | LED
1 | BM70BLES1FC2-0B03AA | BM70BLES1FC2-0B03AA | BM78SPPS5NC2_1 | IC2 | Bluetooth / 802.15.1 Modules |  | Bluetooth / 802.15.1 Modules |  | mm | Microchip | BM70BLES1FC2-0B03AA
1 | BNCPTH | BNCPTH | BNC | J3 | BNC Right Angle Connector |  |  |  |  |  |  |  |  |  |  |  |  |  |  | LPA-12729 |  | PRT-10550
1 | BQ7790504 | BQ77904 | TSSOP-20/6MM | U5 | A battery protection chip with OV/UV/OT/UT |  |  | 296-44599-5-ND
2 | CSD18534Q5A | CSD18534Q5A | TRANS_CSD18534Q5A | Q5, Q6 | 60V N-Channel NexFET Power? MOSFET 8-VSON-FET -55 to 150 | Good | 60V N-Channel NexFET Power? MOSFET 8-VSON-FET -55 to 150 |  |  |  |  | Texas Instruments |  | CSD18534Q5A |  |  |  | VSON-8 Texas Instruments | 0.61 USD
1 | CSTCE12M0G15L99-R0 | CSTCE8M00G52-R0 | CSTCE | C19 |  |  |  |  |  |  | CSTCE8M00G52R0 |  |  |  |  |  |  |  |  |  |  |  |  |  |  | Murata
1 | CTX10-4A-R | CTX10-4A-R | INDM115115X635N | L8 | POWER INDUCTOR | Good | Inductor Power Wirewound 10.53uH/42.11uH 25% 100KHz Amorphous Metal 4.67A/2.33A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 |  |  |  |  | Eaton |  | CTX10-4A-R |  |  |  | Nonstandard Eaton | 3.21 USD
2 | DMN3023L-7 | BSS123 | SOT23 | Q3, Q7 | N-CHANNEL MOS FET
5 | GREEN | LEDCHIP-LED0805 | CHIP-LED0805 | LED2, LED6, LED7, LED8, LED11 | LED
1 | LM1117DTX-ADJ-10V | LM1117DTX-ADJ | TO252 | IC5
1 | LM1117DTX-ADJ-12V | LM1117DTX-ADJ | TO252 | IC3
1 | LM1117DTX-ADJ-3V3 | LM1117DTX-ADJ | TO252 | IC6
1 | LT1513 | LT1513 | TO220-7 | IC1 | Battery Charger Buck/Boost
1 | MBRS330T3 | MBRS330T3 | SMC | D10 | SCHOTTKY BARRIER RECTIFIER 3.0 AMPERES 20, 30, 40 VOLT
1 | MCP111-XXXXX/TO | MCP111-XXXXX/TO | TO-92_MC | U1 |  |  |  |  |  |  | MCP111XXXXXTO |  |  |  |  |  |  |  |  |  |  |  |  |  |  | Microchip
1 | MCP2200-I/SS | MCP2200-I/SS | SSOP20_MC | U3 |  |  |  |  |  |  | mcp2200iss |  |  |  |  |  |  |  |  |  |  |  |  |  |  | Microchip
2 | NC | C-EUC0805 | C0805 | C36, C37 | CAPACITOR, European symbol
3 | NP | CPOL-EUE | PANASONIC_E | C55, C58, C61 | POLARIZED CAPACITOR, European symbol
1 | NTC 103AT | R-EU_M0805 | M0805 | R62 | RESISTOR, European symbol
22 | PTR1B1,27 | PTR1B1,27 | B1,27 | 3V3, BAT_ADC, BAT_PACK_POS, BTN_1, BTN_2, BTN_3, BTN_4, BTN_NRST, BT_RX, BT_TX,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 | TEST PIN
1 | PTR1B2,54 | PTR1B2,54 | B2,54 | RF_SIGNAL | TEST PIN
1 | Power Disconnect | PINHD-1X2 | 1X02 | JP3 | PIN HEADER
1 | RA07H4047M | RA07H4047M | RA07H4047M | U$2
3 | RED | LEDCHIP-LED0805 | CHIP-LED0805 | LED5, LED9, LED12 | LED
1 | S8NC-13 | DIODE-SMC | SMC | D1 | DIODE
1 | STM32L073RZ | STM32L0X3RL | LQFP64-10X10MM | U2 |  |  |  |  |  |  | stm32l0x3rl |  |  |  |  |  |  |  |  |  |  |  |  |  |  | STMicroelectronics
1 | SWD | PINHD-1X5 | 1X05 | PR0> | PIN HEADER
1 | TPD3E001DRLR | TPD3E001DRLR | SOT50P160X60-5N | U4 | LOW-CAPACITANCE 3-CHANNEL ±15-kV ESD-PROTECTION ARRAY FOR HIGH-SPEED DATA INTER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 |  |  |  |  |  |  |  |  |  | TPD3E001DRLR | 1603422 | 41M5842 | SOT-5 |  |  |  |  | Texas Instruments
1 | VIB_MOTOR, 619-28821 | PINHD-1X2 | 1X02 | JP2 | PIN HEADER
1 | WHITE | LEDCHIP-LED0805 | CHIP-LED0805 | LED4 | LED
1 | YELLOW | LEDCHIP-LED0805 | CHIP-LED0805 | LED10 | LED
1 | Zener 16V MMSZ5246BS-7-F | DIODE-SOD323-R | SOD323-R | D6 | DIODE
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

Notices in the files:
eagle/GPS_board/watchplb_gps_v1.0_AB.brd:
Copyright by HSD/ESD 2018
parts and their libraries:
SparkFun-Connectors: Licensing: Creative Commons ShareAlike 4.0 International - https://creativecommons.org/licenses/by-sa/4.0
